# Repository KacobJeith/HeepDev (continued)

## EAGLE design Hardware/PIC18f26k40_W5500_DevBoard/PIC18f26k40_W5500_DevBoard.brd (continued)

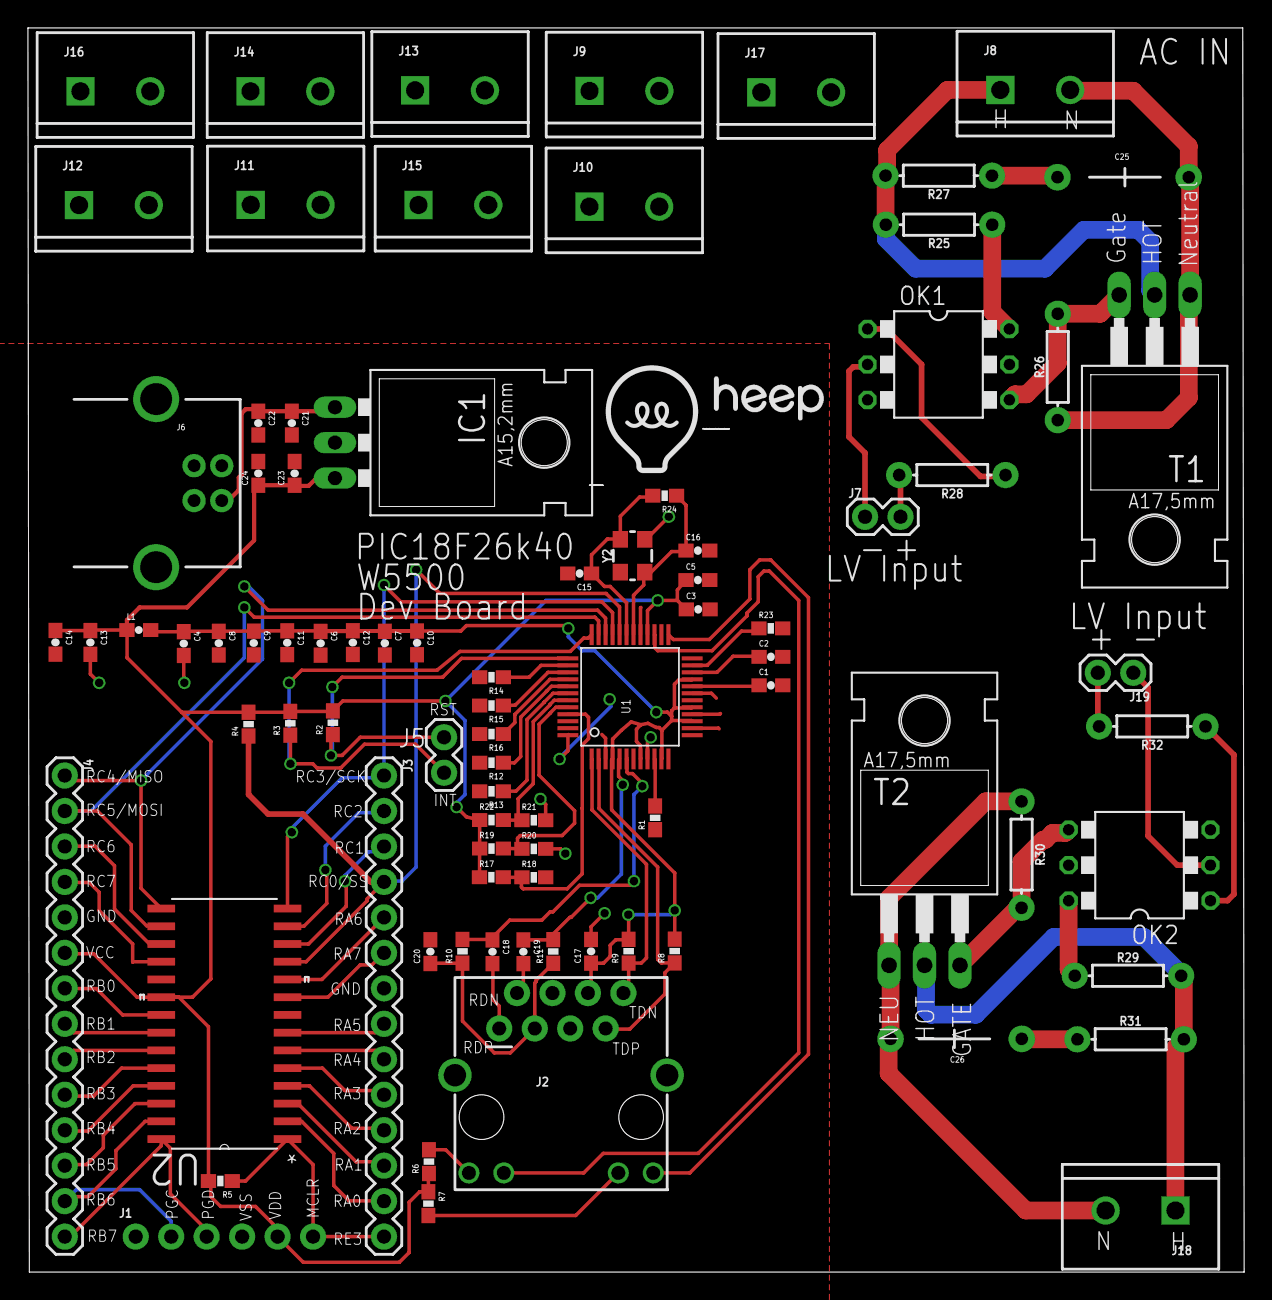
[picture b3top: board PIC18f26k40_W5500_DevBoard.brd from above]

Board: 2 copper layers, 87.1 x 89.1 mm, 88 parts (0 on the bottom side), 72 nets.

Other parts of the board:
U$5: HEEPLOGOSMALL
U$6: HEEPLETTERS

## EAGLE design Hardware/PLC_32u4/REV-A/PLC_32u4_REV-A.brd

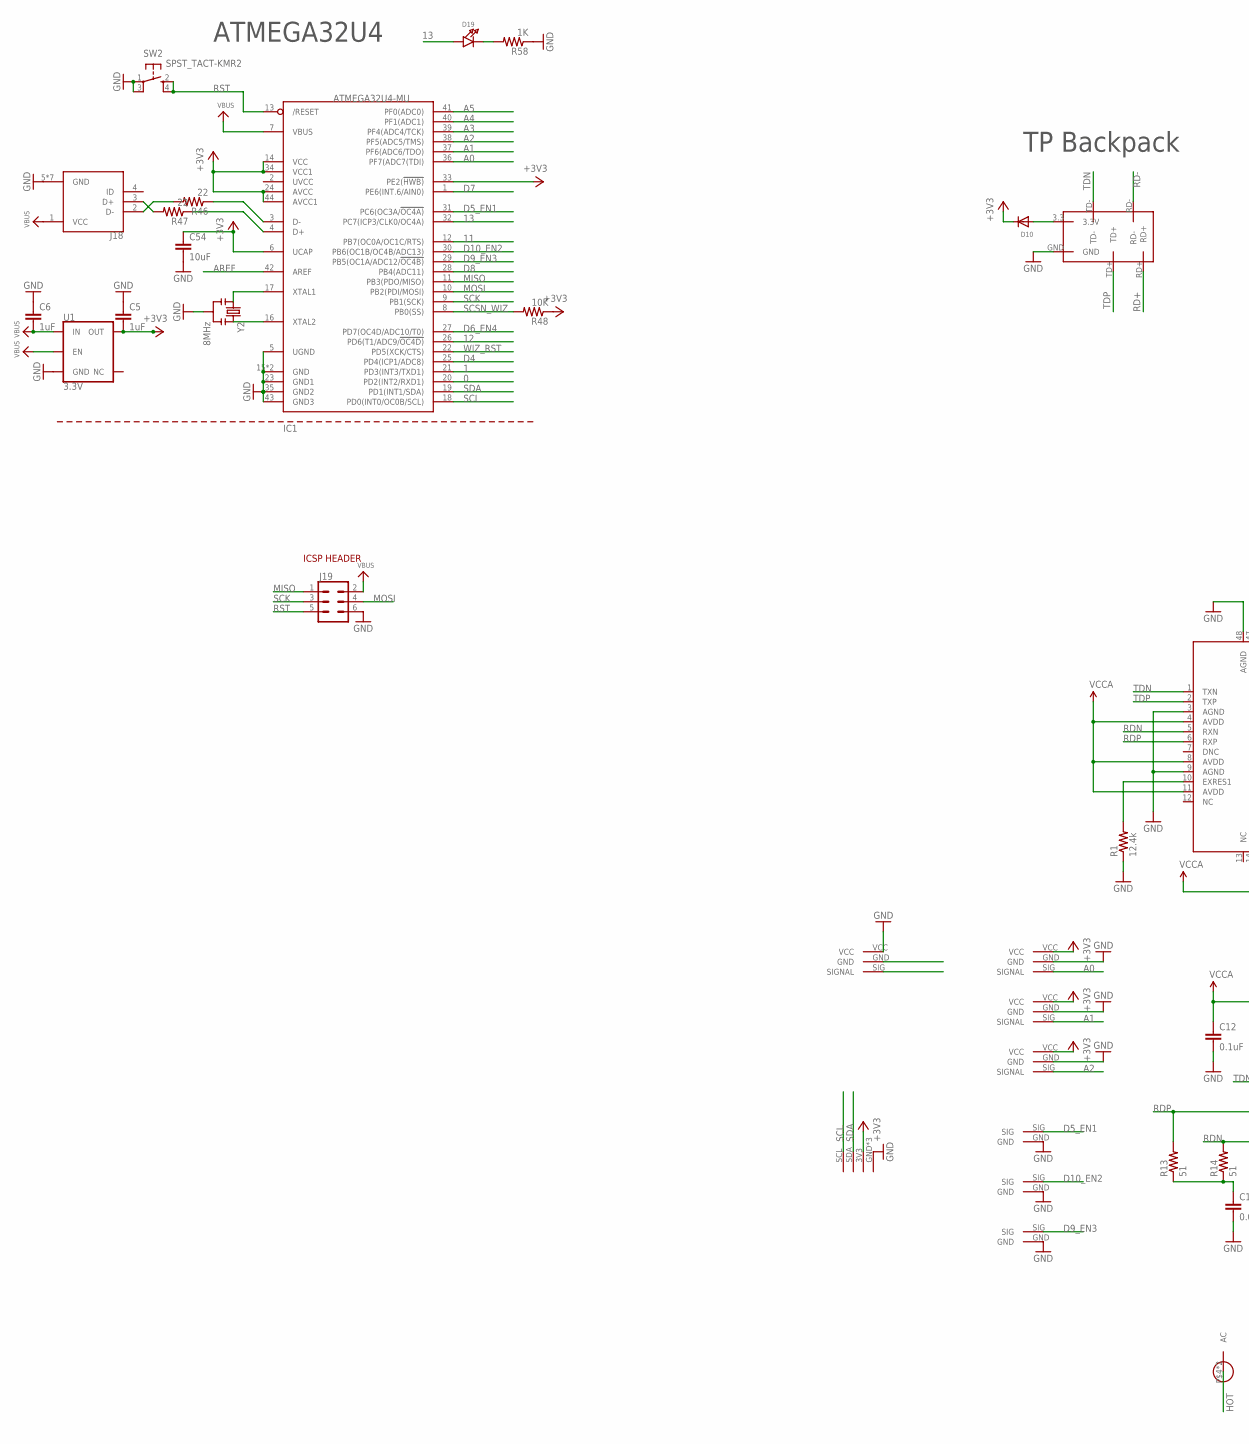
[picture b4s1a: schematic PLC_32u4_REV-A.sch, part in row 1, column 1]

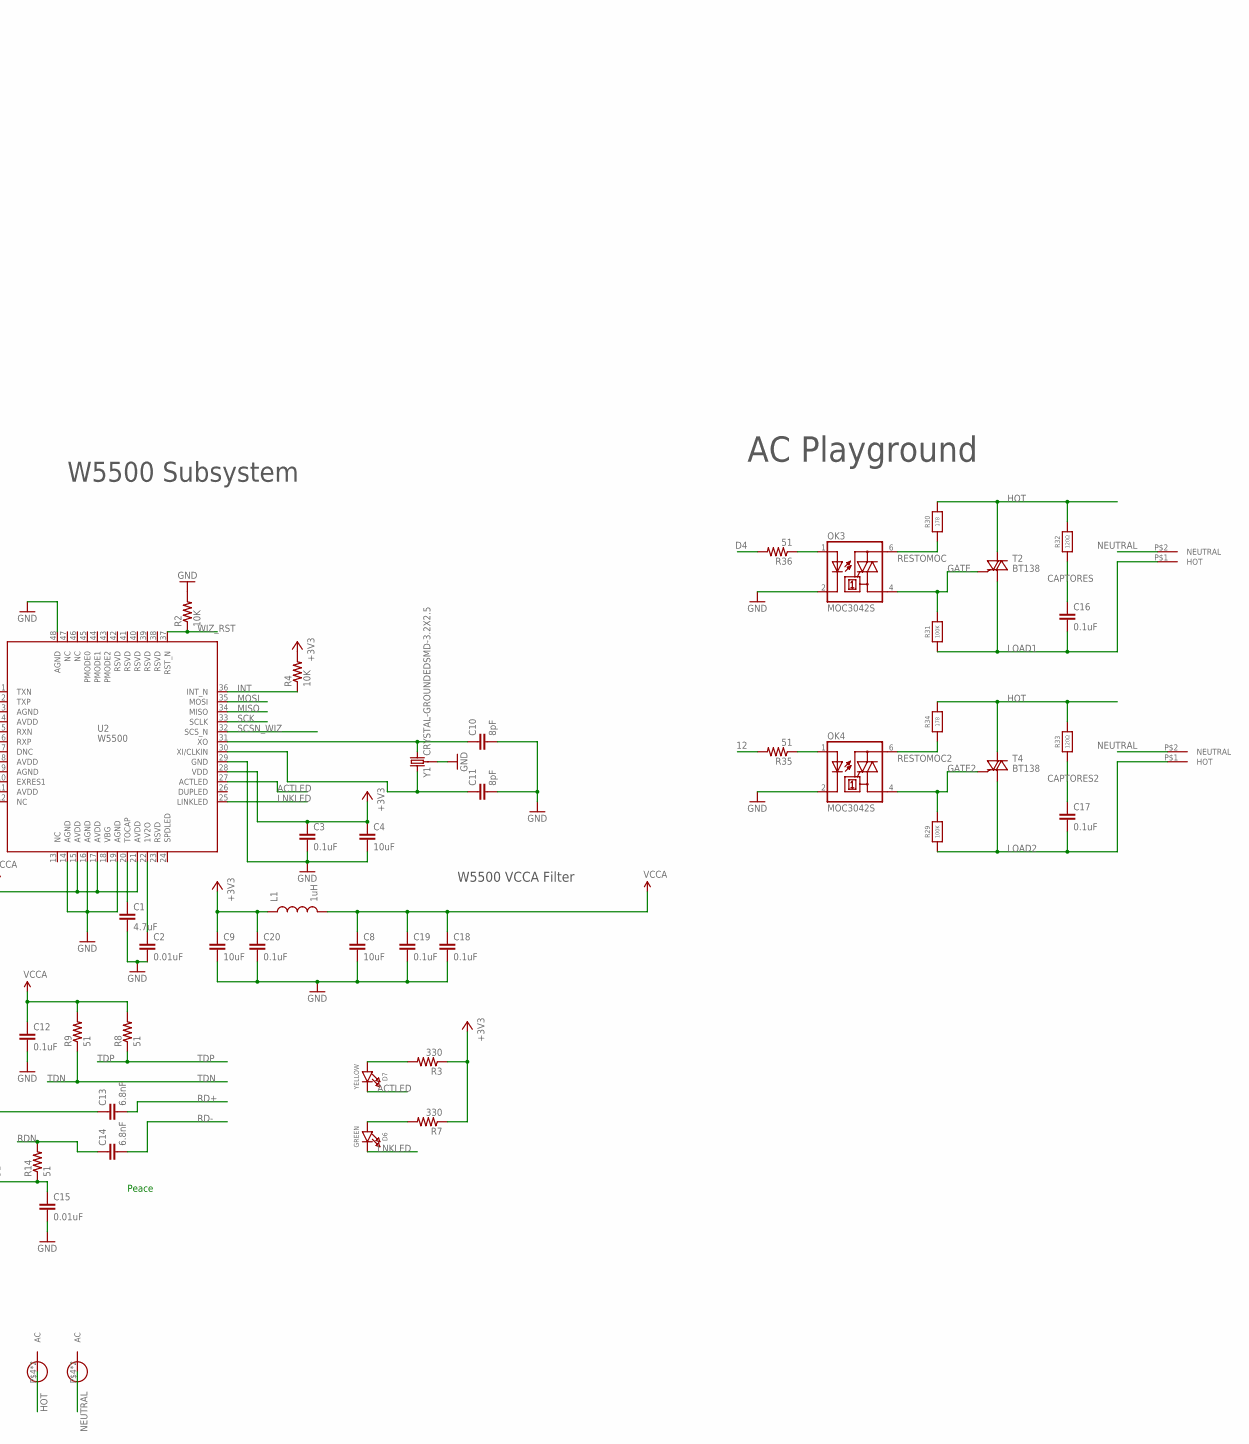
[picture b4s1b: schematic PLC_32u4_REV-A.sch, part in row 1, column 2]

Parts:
C1: 4.7uF; 0603-CAP
C2, C15: 0.01uF; 0603-CAP
C3, C12, C18, C19, C20: 0.1uF; 0603-CAP
C4, C8, C9, C54: 10uF; 0603-CAP
C5, C6: 1uF; 0603-CAP
C10, C11: 8pF; 0603-CAP
C13, C14: 6.8nF; 0603-CAP
C16, C17: 0.1uF; 1210
D6: GREEN; CHIPLED_0603_NOOUTLINE
D7: YELLOW; CHIPLED_0603_NOOUTLINE
D10: DIODESOD-123; SOD-123
D19: LED0805_NOOUTLINE; CHIPLED_0805_NOOUTLINE
IC1: ATMEGA32U4-MU; TQFN44_7MM
J18: 10103594-0001LF; FCI_10103594-0001LF
J19: CONN_03X2NO_SILK; 2X3-NS
L1: 1uH; 0603
OK3, OK4: MOC3042S; DIL6-SMD
R1: 12.4k; 0603-RES
R2, R4, R48: 10K; 0603-RES
R3, R7: 330; 0603-RES
R8, R9, R13, R14, R35, R36: 51; 0603-RES
R29, R31: 100K; 0805_10MGAP
R30, R34: 178; 0805_10MGAP
R32, R33: 120Ω; 0805_10MGAP
R46, R47: 22; 0603-RES
R58: 1K; 0603-RES
SW2: SPST_TACT-KMR2; KMR2
T2, T4: BT138; D2PAK-3
U1: 3.3V; SOT23-5
U2: W5500
U$3: 4P_JST_MINI_MICRO; 4P_JST1.0
U$4, U$26, U$27, U$28: JST_MINI_MICRO; 3P_JST1.0
U$15: TPLINK_BACKPACKMINIMAL_HOLES; BACKPACK_MINIMAL_HOLES
U$22, U$23: AC_BLADE
U$24, U$25: AC_TERMINAL
U$29, U$30, U$31: 2P_JST_MINI_MICRO; 2P_JST1.0
Y1: CRYSTAL-GROUNDEDSMD-3.2X2.5; CRYSTAL-SMD-3.2X2.5MM
Y2: 8MHz; RESONATOR-SMD

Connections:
0: IC1.20 (PD2(INT2/RXD1)), U$4.GND
1: IC1.21 (PD3(INT3/TXD1)), U$4.SIG (SIGNAL)
11: IC1.12 (PB7(OC0A/OC1C/RTS))
12: IC1.26 (PD6(T1/ADC9/!OC4D)), R35.2
13: D19.A, IC1.32 (PC7(ICP3/CLK0/OC4A))
+3V3: C3.1, C4.1, C5.2, C9.1, C20.1, C54.1, D10.C, IC1.6 (UCAP), IC1.14 (VCC), IC1.24 (AVCC), IC1.33 (PE2(!HWB)), IC1.34 (VCC1), IC1.44 (AVCC1), L1.1, R3.1, R4.2, R7.1, R48.1, U1.5 (OUT), U2.28 (VDD), U$3.3V3, U$26.VCC, U$27.VCC, U$28.VCC
A0: IC1.36 (PF7(ADC7(TDI)), U$28.SIG (SIGNAL)
A1: IC1.37 (PF6(ADC6/TDO)), U$26.SIG (SIGNAL)
A2: IC1.38 (PF5(ADC5/TMS)), U$27.SIG (SIGNAL)
A3: IC1.39 (PF4(ADC4/TCK))
A4: IC1.40 (PF1(ADC1))
A5: IC1.41 (PF0(ADC0))
ACTLED: D7.C, U2.27 (ACTLED)
AREF: IC1.42 (AREF)
CAPTORES: C16.1, R32.1
CAPTORES2: C17.1, R33.1
D4: IC1.25 (PD4(ICP1/ADC8)), R36.2
D5_EN1: IC1.31 (PC6(OC3A/!OC4A)), U$31.SIG
D6_EN4: IC1.27 (PD7(OC4D/ADC10/T0))
D7: IC1.1 (PE6(INT.6/AIN0))
D8: IC1.28 (PB4(ADC11))
D9_EN3: IC1.29 (PB5(OC1A/ADC12/!OC4B)), U$29.SIG
D10_EN2: IC1.30 (PB6(OC1B/OC4B/ADC13)), U$30.SIG
D+1: IC1.4 (D+), R47.1
D-1: IC1.3 (D-), R46.1
GATE: OK3.4 (A1), R31.2, T2.G
GATE2: OK4.4 (A1), R29.2, T4.G
GND: C1.2, C2.2, C3.2, C4.2, C5.1, C6.1, C8.2, C9.2, C10.2, C11.2, C12.2, C15.2, C18.2, C19.2, C20.2, C54.2, IC1.5 (UGND), IC1.15 (GND), IC1.23 (GND1), IC1.35 (GND2), IC1.43 (GND3), IC1.THERMAL (GND), J18.5 (GND), J18.P1 (GND), J18.P2 (GND), J18.P3 (GND), J18.P4 (GND), J18.P5 (GND), J18.P6 (GND), J19.6, OK3.2 (C), OK4.2 (C), R1.1, R2.2, R58.1, SW2.1, SW2.3 (P1), U1.2 (GND), U2.3 (AGND), U2.9 (AGND), U2.14 (AGND), U2.16 (AGND), U2.19 (AGND), U2.29 (GND), U2.48 (AGND), U$3.GND, U$3.P$4 (GND), U$3.P$5 (GND), U$4.VCC, U$15.GND, U$26.GND, U$27.GND, U$28.GND, U$29.GND, U$30.GND, U$31.GND, Y1.2 (3), Y1.4 (3), Y2.2
HOT: R30.2, R32.2, R33.2, R34.2, T2.A2, T4.A2, U$22.P$4, U$22.P$5
INT: R4.1, U2.36 (INT_N)
LNKLED: D6.C, U2.25 (LINKLED)
LOAD1: C16.2, R31.1, T2.A1, U$25.P$1 (HOT)
LOAD2: C17.2, R29.1, T4.A1, U$24.P$1 (HOT)
MISO: IC1.11 (PB3(PDO/MISO)), J19.1, U2.34 (MISO)
MOSI: IC1.10 (PB2(PDI/MOSI)), J19.4, U2.35 (MOSI)
unnamed: C1.1, U2.20 (TOCAP)
unnamed: C2.1, U2.22 (1V2O)
unnamed: R1.2, U2.10 (EXRES1)
unnamed: D7.A, R3.2
unnamed: D6.A, R7.2
unnamed: C15.1, R13.1, R14.1
unnamed: C10.1, U2.31 (XO), Y1.3 (2)
unnamed: C11.1, U2.30 (XI/CLKIN), Y1.1
unnamed: OK3.1 (A), R36.1
unnamed: OK4.1 (A), R35.1
unnamed: D10.A, U$15.3.3 (3.3V)
unnamed: IC1.16 (XTAL2), Y2.3
unnamed: IC1.17 (XTAL1), Y2.1
unnamed: J18.3 (D+), R47.2
unnamed: J18.2 (D-), R46.2
unnamed: D19.C, R58.2
NEUTRAL: U$23.P$4, U$23.P$5, U$24.P$2 (NEUTRAL), U$25.P$2 (NEUTRAL)
RD+: C13.2, U$15.RD+
RD-: C14.2, U$15.RD-
RDN: C14.1, R14.2, U2.5 (RXN)
RDP: C13.1, R13.2, U2.6 (RXP)
RESTOMOC: OK3.6 (A2), R30.1
RESTOMOC2: OK4.6 (A2), R34.1
RST: IC1.13 (/RESET), J19.5, SW2.2 (S), SW2.4 (S1)
SCK: IC1.9 (PB1(SCK)), J19.3, U2.33 (SCLK)
SCL: IC1.18 (PD0(INT0/OC0B/SCL)), U$3.SCL
SCSN_WIZ: IC1.8 (PB0(SS)), R48.2, U2.32 (SCS_N)
SDA: IC1.19 (PD1(INT1/SDA)), U$3.SDA
TDN: R9.1, U2.1 (TXN), U$15.TD-
TDP: R8.1, U2.2 (TXP), U$15.TD+
VBUS: C6.2, IC1.7 (VBUS), J18.1 (VCC), J19.2, U1.1 (IN), U1.3 (EN)
VCCA: C8.1, C12.1, C18.1, C19.1, L1.2, R8.2, R9.2, U2.4 (AVDD), U2.8 (AVDD), U2.11 (AVDD), U2.15 (AVDD), U2.17 (AVDD), U2.21 (AVDD)
WIZ_RST: IC1.22 (PD5(XCK/CTS)), R2.1, U2.37 (RST_N)

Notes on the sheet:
W5500 Subsystem
W5500 VCCA Filter
AC Playground
TP Backpack
Peace
ATMEGA32U4
ICSP HEADER

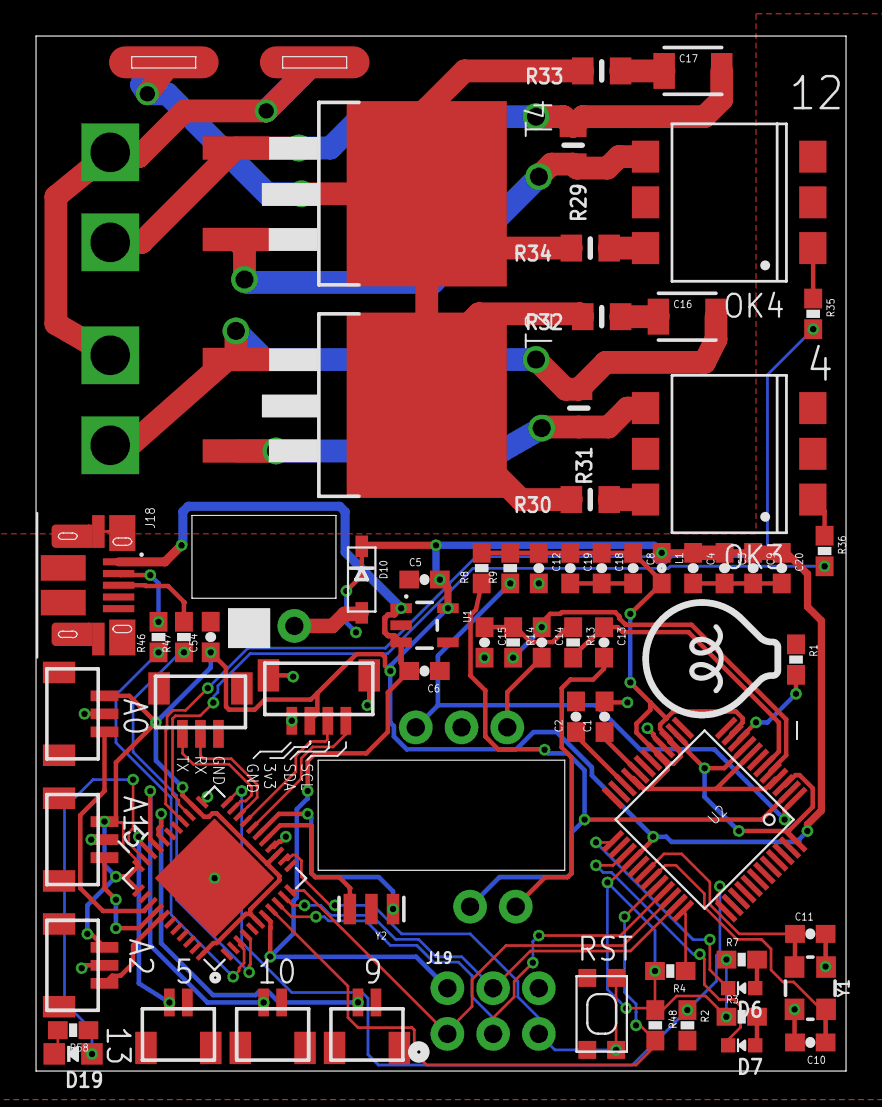
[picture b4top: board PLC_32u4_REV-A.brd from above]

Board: 2 copper layers, 45.0 x 57.5 mm, 72 parts (0 on the bottom side), 60 nets.

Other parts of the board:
U$32: HEEPLOGOSMALL

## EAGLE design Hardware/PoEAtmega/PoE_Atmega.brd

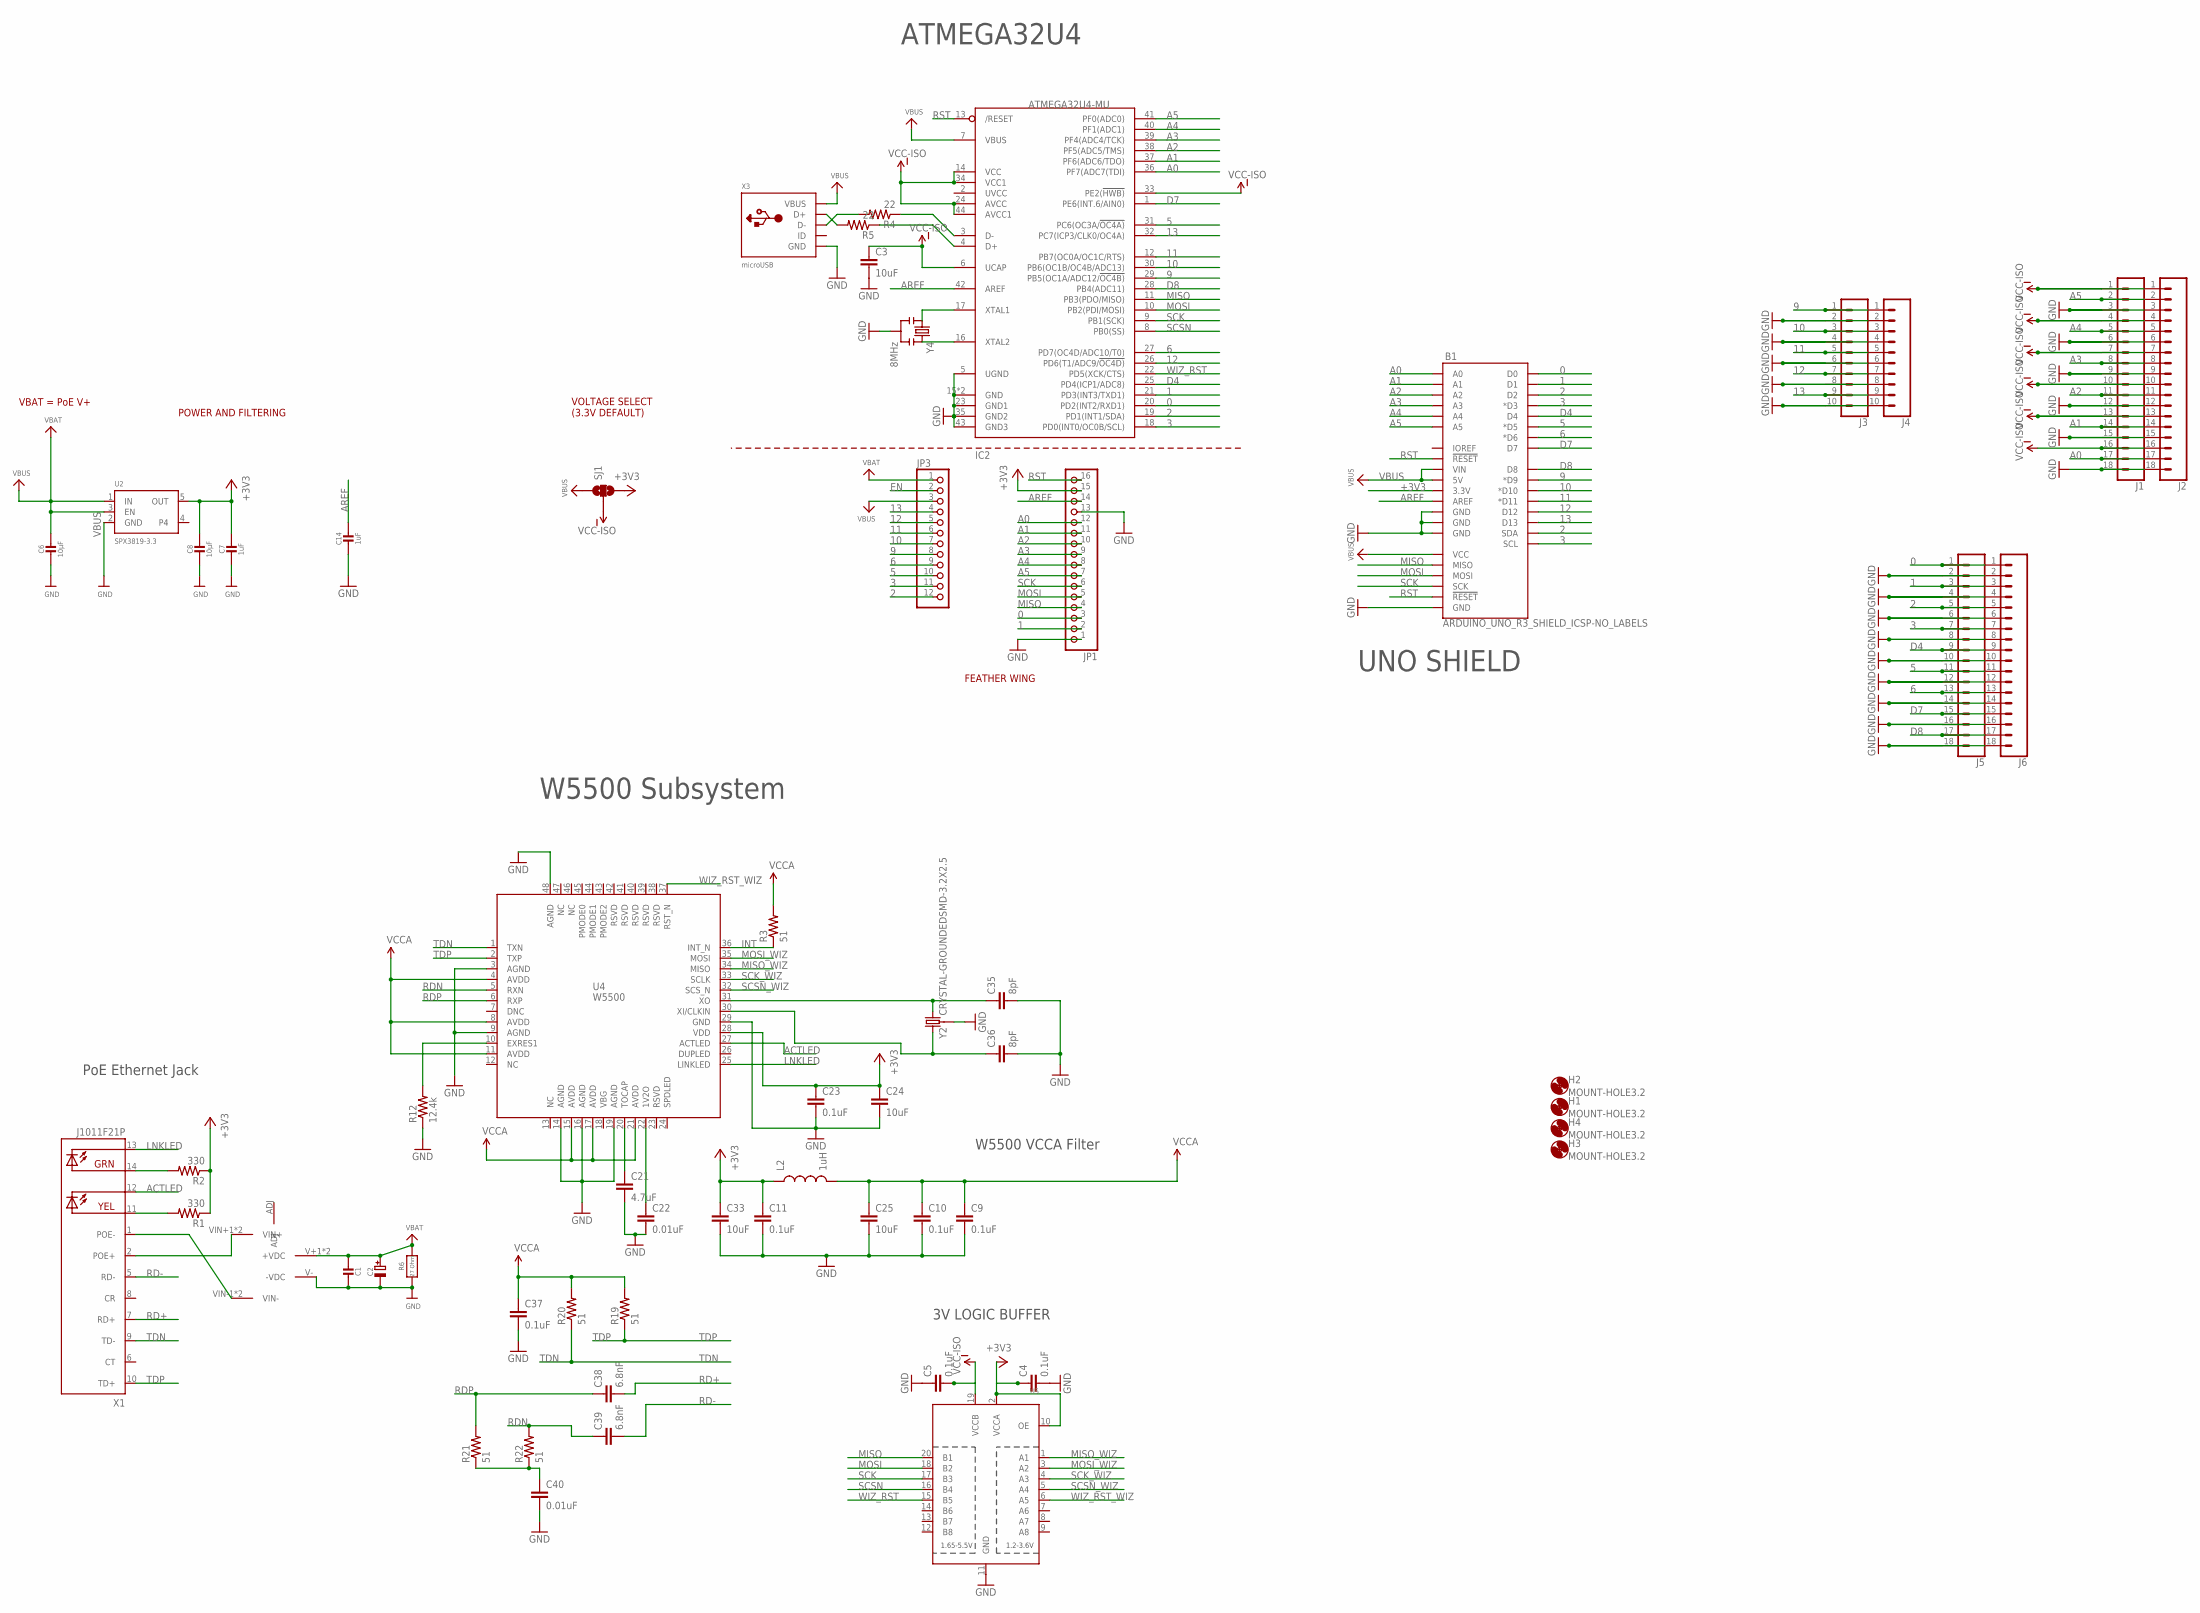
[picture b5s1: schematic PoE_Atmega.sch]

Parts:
B1: ARDUINO_UNO_R3_SHIELD_ICSP-NO_LABELS; UNO_R3_SHIELD_ICSP_NOLABELS
C1: CAP_CERAMIC_0805MP; _0805MP
C2: CAP_ELECTROLYTICPANASONIC_C; PANASONIC_C
C3, C24, C25, C33: 10uF; 0603-CAP
C4, C5, C9, C10, C11, C23, C37: 0.1uF; 0603-CAP
C6, C8: 10µF; 0603-MINI
C7: 1uF; 0603-MINI
C14: 1uF; 0603-NO
C21: 4.7uF; 0603-CAP
C22, C40: 0.01uF; 0603-CAP
C35, C36: 8pF; 0603-CAP
C38, C39: 6.8nF; 0603-CAP
H1, H2, H3, H4: MOUNT-HOLE3.2; 3,2
IC2: ATMEGA32U4-MU; TQFN44_7MM
J1, J2, J5, J6: CONN_18; 1X18
J3, J4: CONN_10"; 1X10
JP1: HEADER-1X16ROUND; 1X16_ROUND
JP3: HEADER-1X12; 1X12_ROUND
L2: 1uH; 0603
R1, R2: 330; 0603-RES
R3, R19, R20, R21, R22: 51; 0603-RES
R4, R5: 22; 0603-RES
R6: 27 Ohm; 2512
R12: 12.4k; 0603-RES
SJ1: SOLDERJUMPER_2WAYPASTE2&3; SJ_3_PASTE2&3
U2: SPX3819-3.3; SOT23-5
U4: W5500
U5: TXB0108PWR; TSSOP20
U$1: SILVERTEL_POEMICRO; AG9900
X1: J1011F21P; J1
X3: microUSB; 4UCONN_20329_V2
Y2: CRYSTAL-GROUNDEDSMD-3.2X2.5; CRYSTAL-SMD-3.2X2.5MM
Y4: 8MHz; RESONATOR-SMD

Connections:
0: B1.RX (D0), IC2.20 (PD2(INT2/RXD1)), J5.1, J6.1, JP1.3
1: B1.TX (D1), IC2.21 (PD3(INT3/TXD1)), J5.3, J6.3, JP1.2
2: B1.D2, B1.SDA, IC2.19 (PD1(INT1/SDA)), J5.5, J6.5, JP3.12
3: B1.D3 (*D3), B1.SCL, IC2.18 (PD0(INT0/OC0B/SCL)), J5.7, J6.7, JP3.11
5: B1.D5 (*D5), IC2.31 (PC6(OC3A/!OC4A)), J5.11, J6.11, JP3.10
6: B1.D6 (*D6), IC2.27 (PD7(OC4D/ADC10/T0)), J5.13, J6.13, JP3.9
9: B1.D9 (*D9), IC2.29 (PB5(OC1A/ADC12/!OC4B)), J3.1, J4.1, JP3.8
10: B1.D10 (*D10), IC2.30 (PB6(OC1B/OC4B/ADC13)), J3.3, J4.3, JP3.7
11: B1.D11 (*D11), IC2.12 (PB7(OC0A/OC1C/RTS)), J3.5, J4.5, JP3.6
12: B1.D12, IC2.26 (PD6(T1/ADC9/!OC4D)), J3.7, J4.7, JP3.5
13: B1.D13, IC2.32 (PC7(ICP3/CLK0/OC4A)), J3.9, J4.9, JP3.4
+3V3: B1.3.3V, C4.1, C7.1, C8.1, C11.1, C23.1, C24.1, C33.1, JP1.15, L2.1, R1.1, R2.1, SJ1.3, U2.5 (OUT), U4.28 (VDD), U5.2 (VCCA), U5.10 (OE)
A0: B1.A0, IC2.36 (PF7(ADC7(TDI)), J1.17, J2.17, JP1.12
A1: B1.A1, IC2.37 (PF6(ADC6/TDO)), J1.14, J2.14, JP1.11
A2: B1.A2, IC2.38 (PF5(ADC5/TMS)), J1.11, J2.11, JP1.10
A3: B1.A3, IC2.39 (PF4(ADC4/TCK)), J1.8, J2.8, JP1.9
A4: B1.A4, IC2.40 (PF1(ADC1)), J1.5, J2.5, JP1.8
A5: B1.A5, IC2.41 (PF0(ADC0)), J1.2, J2.2, JP1.7
ACTLED: U4.27 (ACTLED), X1.12 (YEL-C)
AREF: B1.AREF, C14.1, IC2.42 (AREF), JP1.14
D4: B1.D4, IC2.25 (PD4(ICP1/ADC8)), J5.9, J6.9
D7: B1.D7, IC2.1 (PE6(INT.6/AIN0)), J5.15, J6.15
D8: B1.D8, IC2.28 (PB4(ADC11)), J5.17, J6.17
D+: IC2.4 (D+), R5.1
D-: IC2.3 (D-), R4.1
EN: JP3.2
GND: B1.GND@0 (GND), B1.GND@1 (GND), B1.GND@2 (GND), B1.GND_ICSP (GND), C1.1, C2.-, C3.2, C4.2, C5.1, C6.2, C7.2, C8.2, C9.2, C10.2, C11.2, C14.2, C21.2, C22.2, C23.2, C24.2, C25.2, C33.2, C35.2, C36.2, C37.2, C40.2, IC2.5 (UGND), IC2.15 (GND), IC2.23 (GND1), IC2.35 (GND2), IC2.43 (GND3), IC2.THERMAL (GND), J1.3, J1.6, J1.9, J1.12, J1.15, J1.18, J2.3, J2.6, J2.9, J2.12, J2.15, J2.18, J3.2, J3.4, J3.6, J3.8, J3.10, J4.2, J4.4, J4.6, J4.8, J4.10, J5.2, J5.4, J5.6, J5.8, J5.10, J5.12, J5.14, J5.16, J5.18, J6.2, J6.4, J6.6, J6.8, J6.10, J6.12, J6.14, J6.16, J6.18, JP1.1, JP1.13, R6.1, R12.1, U2.2 (GND), U4.3 (AGND), U4.9 (AGND), U4.14 (AGND), U4.16 (AGND), U4.19 (AGND), U4.29 (GND), U4.48 (AGND), U5.11 (GND), U$1.V- (-VDC), X3.BASE@1 (GND), X3.BASE@2 (GND), X3.GND, X3.SPRT@1 (GND), X3.SPRT@2 (GND), X3.SPRT@3 (GND), X3.SPRT@4 (GND), Y2.2 (3), Y4.2; also elsewhere on the board
INT: R3.1, U4.36 (INT_N)
LNKLED: U4.25 (LINKLED), X1.13 (GRN-C)
MISO: B1.MISO, IC2.11 (PB3(PDO/MISO)), JP1.4, U5.20 (B1)
MISO_WIZ: U4.34 (MISO), U5.1 (A1)
MOSI: B1.MOSI, IC2.10 (PB2(PDI/MOSI)), JP1.5, U5.18 (B2)
MOSI_WIZ: U4.35 (MOSI), U5.3 (A2)
unnamed: U$1.VIN-1 (VIN-), U$1.VIN-2 (VIN-), X1.1 (POE-)
unnamed: U$1.VIN+1 (VIN+), U$1.VIN+2 (VIN+), X1.2 (POE+)
unnamed: R5.2, X3.D+
unnamed: R1.2, X1.11 (YEL-A)
unnamed: R2.2, X1.14 (GRN-A)
unnamed: IC2.16 (XTAL2), Y4.3
unnamed: IC2.17 (XTAL1), Y4.1
unnamed: R4.2, X3.D-
unnamed: C21.1, U4.20 (TOCAP)
unnamed: C22.1, U4.22 (1V2O)
unnamed: R12.2, U4.10 (EXRES1)
unnamed: C40.1, R21.1, R22.1
unnamed 45: C35.1, U4.31 (XO), Y2.3 (2); also elsewhere on the board
unnamed 46: C36.1, U4.30 (XI/CLKIN), Y2.1; also elsewhere on the board
RD+: C38.2, X1.7 (RD+)
RD-: C39.2, X1.5 (RD-)
RDN: C39.1, R22.2, U4.5 (RXN)
RDP: C38.1, R21.2, U4.6 (RXP)
RST: B1.RES (!RESET!), B1.RST_ICSP (!RESET!), IC2.13 (/RESET), JP1.16
SCK: B1.SCK, IC2.9 (PB1(SCK)), JP1.6, U5.17 (B3)
SCK_WIZ: U4.33 (SCLK), U5.4 (A3)
SCSN: IC2.8 (PB0(SS)), U5.16 (B4)
SCSN_WIZ: U4.32 (SCS_N), U5.5 (A4)
TDN: R20.1, U4.1 (TXN), X1.9 (TD-)
TDP: R19.1, U4.2 (TXP), X1.10 (TD+)
VBAT: JP3.1
VBUS: B1.5V, B1.5V_ICSP (VCC), B1.VIN, C1.2, C2.+, C6.1, IC2.7 (VBUS), JP3.3, R6.2, SJ1.1, U2.1 (IN), U2.3 (EN), U$1.V+1 (+VDC), U$1.V+2 (+VDC), X3.VBUS
VCC-ISO: C3.1, C5.2, IC2.6 (UCAP), IC2.14 (VCC), IC2.24 (AVCC), IC2.33 (PE2(!HWB)), IC2.34 (VCC1), IC2.44 (AVCC1), J1.1, J1.4, J1.7, J1.10, J1.13, J1.16, J2.1, J2.4, J2.7, J2.10, J2.13, J2.16, SJ1.2, U5.19 (VCCB)
VCCA: C9.1, C10.1, C25.1, C37.1, L2.2, R3.2, R19.2, R20.2, U4.4 (AVDD), U4.8 (AVDD), U4.11 (AVDD), U4.15 (AVDD), U4.17 (AVDD), U4.21 (AVDD)
WIZ_RST: IC2.22 (PD5(XCK/CTS)), U5.15 (B5)
WIZ_RST_WIZ: U4.37 (RST_N), U5.6 (A5)

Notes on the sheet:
W5500 Subsystem
W5500 VCCA Filter
FEATHER WING
POWER AND FILTERING
VBAT = PoE V+
VOLTAGE SELECT (3.3V DEFAULT)
PoE Ethernet Jack
UNO SHIELD
3V LOGIC BUFFER
ATMEGA32U4

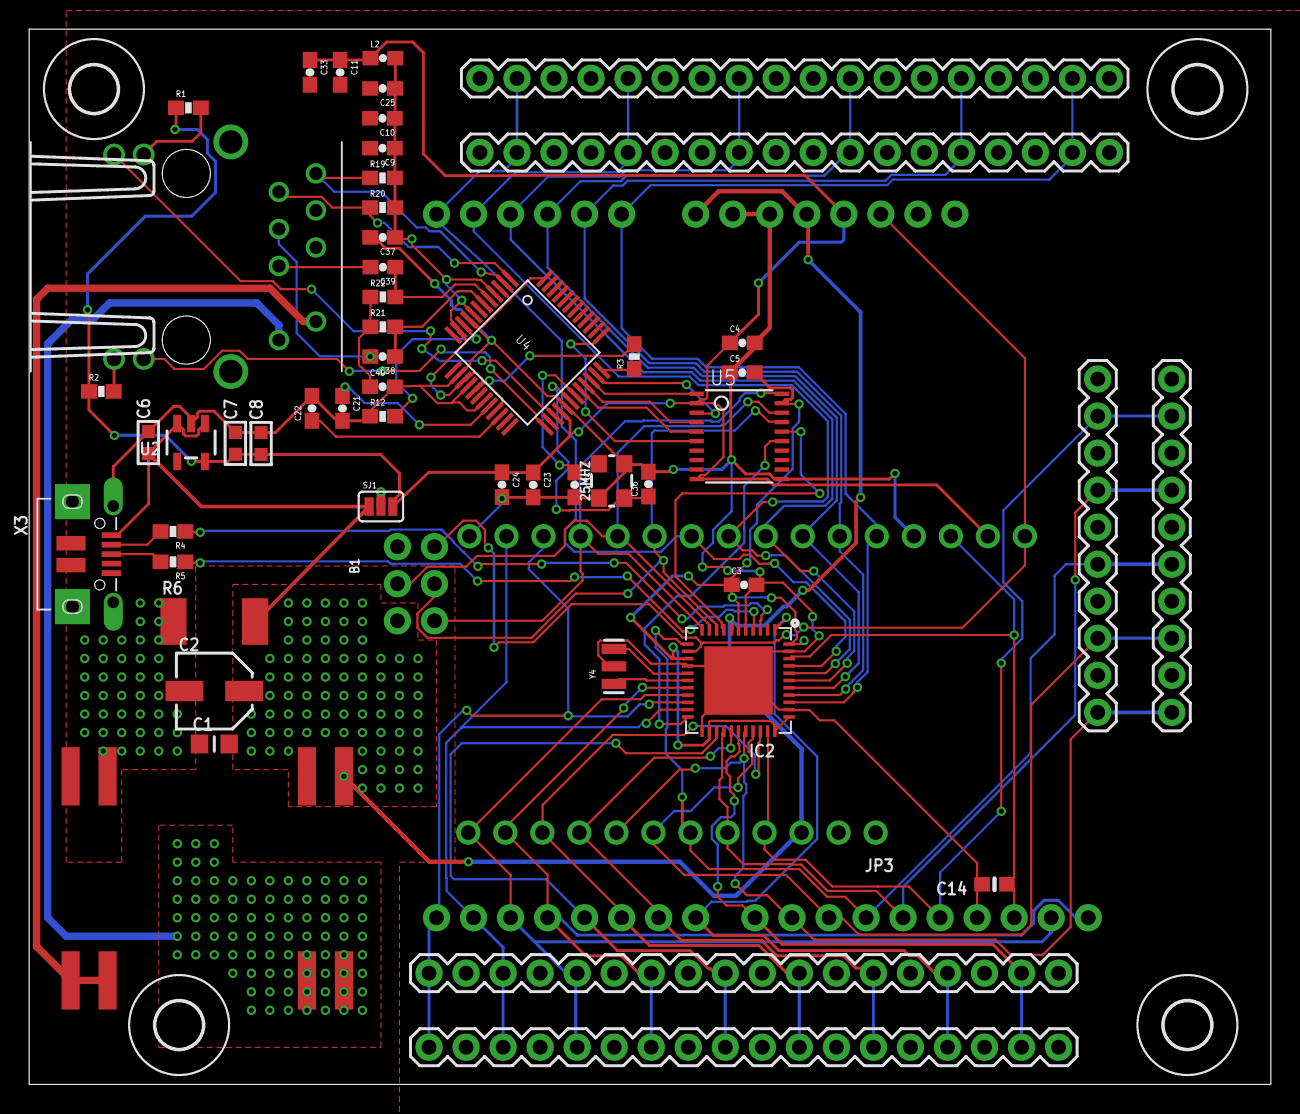
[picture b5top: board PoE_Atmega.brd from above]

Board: 2 copper layers, 85.2 x 72.4 mm, 59 parts (1 on the bottom side), 62 nets.

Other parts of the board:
25MHZ: CRYSTAL-GROUNDEDSMD-3.2X2.5; CRYSTAL-SMD-3.2X2.5MM

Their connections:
GND: 25MHZ.2, 25MHZ.4; also elsewhere on the board
unnamed 45: 25MHZ.3; also elsewhere on the board
unnamed 46: 25MHZ.1; also elsewhere on the board
